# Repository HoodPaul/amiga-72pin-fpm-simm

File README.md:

# Amiga 72-pin FPM SIMM

A common PCB for **4 MB single-sided** and **8 MB double-sided** 5 V FPM SIMMs, developed for Amiga 4000 motherboard memory configurations. Current revision: **A7**.

The project began with a wish to make RAM that visually matches Re-Amiga systems: **black PCB, white silkscreen and gold contacts and exposed pads**. It is a collaboration between **Paul of UK Computing Limited**, **Jon of JMC Electronics** and **AI assistance through Codex**.

**FIRST SUCCESSFUL HARDWARE TEST: 7 November 2026.** Five custom Rev A7 SIMMs installed in an Amiga 4000D were recognised by Kickstart Memory Scan as **18.00 MB total (2.00 MB Chip RAM + 16.00 MB Fast RAM)**. The Chip RAM socket contained one physically **8 MB double-sided** module, recognised as **2 MB Chip RAM**; the four Fast RAM sockets contained four **4 MB front-only** modules. Paul reports the machine alive and working. This establishes initial detection and operation, not a completed extended memory, refresh, retention or graphics/DMA diagnostic. See the [first hardware test report](docs/2026-11-07-FIRST-A4000D-HARDWARE-TEST.md).

**Previous manufacturing milestone, 24 October 2026:** All 15 JLCPCB PCBs were reported manufactured and in transit. Five have since been assembled and demonstrated in the host. Exact receipt date, full shipment count and finished-board measurements have not been recorded. See the [manufacturing record](docs/FABRICATION-OPTIONS.md) and [production-file review](docs/JLCPCB-PRODUCTION-REVIEW.md).

For another engineer or AI picking up the project, start with [AGENTS.md](AGENTS.md), the [current AI handover](docs/AI-HANDOVER.md) and the [documentation index](docs/README.md).

These are unpopulated CAD appearance previews: black solder mask, white silkscreen and gold exposed pads. Actual colours and contact plating are fabrication choices.

## PCB and files

Open [HY8M-SIMM.kicad_pro](HY8M-SIMM.kicad_pro) with **KiCad 10.0 or newer**. Project-local symbols and footprints are included.

| Property | Current design |
|---|---|
| Connector | 72-pin SIMM, 32-bit non-parity |
| Outline | 107.95 × 25.4 mm |
| Finished thickness | 1.2 mm ordered; measure finished boards and verify socket fit |
| Copper layers | **Four** |
| F.Cu | Front signals and pads |
| In1.Cu | GND plane |
| In2.Cu | Signals and +5 V copper fill |
| B.Cu | Rear signals and pads |
| Minimum signal track / nominal clearance | 0.20 / 0.20 mm |
| Through vias | 0.60 mm copper diameter / 0.30 mm drill |

In2.Cu is a mixed signal/supply layer. The design does not have separate GND and power planes on this four-layer PCB.

## 70 ns assembly options

Both builds use **HY5118160JC-70** DRAMs and the same PCB. DNP means do not populate.

| Build | DRAM population | Capacitors fitted | R1/R2 | R3/R4 | PD links fitted |
|---|---|---|---|---|---|
| [4 MB / 70 ns](variants/4MB-70ns/BOM.csv) | U1/U2, front only | C1/C2 | DNP | DNP | PD1, PD2, PD3 |
| [8 MB / 70 ns](variants/8MB-70ns/BOM.csv) | U1–U4, both faces | C1–C4 | 0 Ω each | 10 kΩ each | PD3 |

Capacitors are **220 nF (0.22 µF), 0805, X7R, 16 V or higher**. Use new capacitors. Links and pull-ups use 0603 pads. PD4 remains open in both builds.

Separate [60 ns variants](assembly-options.csv) are retained for the verified **HY5118160BJC-60** part. Use the chosen variant's BOM and DNP-marked schematic. Fitting different PD links cannot make a 70 ns chip operate as a 60 ns part.

A true 4 MB single-sided build omits U3/U4, C3/C4 and R1–R4. Disabling the rear rank of a physically double-sided board does not make it a single-sided module for socket clearance.

## Intended Amiga configurations

| Purpose | Intended population |
|---|---|
| 2 MB Chip RAM | One fully populated 8 MB module; intended to use 2 MB and leave 6 MB unaddressed |
| 16 MB Fast RAM | Two 8 MB modules in Fast slots 1 and 3 |
| 16 MB Fast RAM | Four front-only 4 MB modules in Fast slots 1–4 |

Fast-slot numbering excludes the separate Chip RAM socket. **The 8 MB physical Chip module used as 2 MB Chip RAM and four 4 MB Fast modules have now been recognised together on an A4000D (7 November 2026)**. The alternative two-8 MB Fast RAM configuration remains untested. The Chip RAM socket does not gain 8 MB of addressable Chip RAM. See [hardware test evidence](docs/2026-11-07-FIRST-A4000D-HARDWARE-TEST.md) and [compatibility research](docs/compatibility-research.md).

## Donor chips

The Hyundai HY5118160 devices were chosen for their relatively low SOJ package profile and the availability of suitable donor SIMMs on online marketplaces during project planning. This made them a practical starting point for the matching modules while keeping one chip family across the 4 MB and 8 MB builds.

Obtain readable photographs of **every fitted chip on both faces** before buying a donor. The specified 70 ns device is **HY5118160JC-70**: 5 V, 1M×16, FPM, 42-pin 400 mil SOJ, 1K refresh. The separately verified 60 ns alternative is **HY5118160BJC-60**.

An “8 MB / 2M×32 / 72-pin” listing or bare PCB number does not identify its chips. **HY5118164 is EDO**, and **HY5116160B has a different refresh organisation**; neither is the specified donor. Confirm the complete marking and datasheet rather than relying on similar part numbers.

### Most likely alternative DRAMs (not yet tested)

The **LG/GoldStar GM71C18160CJ-7 (70 ns)**, **GM71C18160CJ-6 (60 ns)**, **Samsung KM416C1200AJ-7 (70 ns)** and **KM416C1200AJ-6 (60 ns)** are promising **5 V, 1M × 16, FPM, 1K-refresh, 42-pin SOJ** candidates. **All four remain untested on Rev A7**, with no proven donor-board or Amiga hardware result. Confirm the exact part's pinout, package, refresh and timing before using it. See the [LG/Samsung alternative comparison and source links](docs/compatibility-research.md#high-confidence-lggoldstar-and-samsung-alternatives-untested-9-november-2026).

Test the intact donor before desoldering and record orientation/pin 1. One healthy four-chip donor can supply one 8 MB board or two 4 MB boards, assuming all devices survive removal. This project does not certify donor authenticity, seller stock or recovered-chip health.

## Prototype fabrication and remaining checks

- **Current order:** four layers, 1.2 mm nominal, 1 oz copper on all layers, black mask, white silkscreen, **ENIG 2 microinch**, ink-plugged vias, **no bevel**, deburring, no edge plating and no manufacturer mark. See the [ordering settings and screenshots](docs/FABRICATION-OPTIONS.md).
- **Contacts:** the native pad setback is **0.2286 mm**; CAM copper compensation leaves approximately **0.221 mm**. The original 144 findings against the generic 0.50 mm edge rule remain documented. The reviewed CAM preserves all contacts and functional connections; this is specific to this prototype package, not blanket approval for other manufacturers or bevel processes.
- **Finish and fit:** the selected ENIG prototype finish differs from the earlier selective hard-gold proposal. Hard gold offers better wear resistance for repeated insertion. Measure the finished connector thickness and inspect edge quality, SOJ fit and socket/case clearance before use. Substantial hand bevelling could cut into the plated contacts.

The retaining holes are closed circular Edge.Cuts profiles in the source; JLCPCB converted these to **3.18 mm finished non-plated holes** with compensated 3.25 mm tools. Use the [four-layer file map](docs/layer-file-map.txt) and read [fabrication notes](fabrication-review/READ-BEFORE-ORDERING.txt). The common paste layers include all footprints; assembly/stencil use must follow the chosen BOM.

## Checks and limitations

The saved design has **864 track segments, 195 vias and zero unconnected items**. The [exact copper comparison](docs/copper-comparison.txt) confirms unchanged routing, pads, component placements, outline and filled copper between A3–A6, the user-edited PCB and A7. The independent mapping review passes 321 assertions.

**144 contact-edge errors and 46 schematic-parity warnings remain documented.** Existing project settings ignore seven check types; no ERC report is included. Read [validation.txt](docs/validation.txt) and the [native DRC report](docs/drc-routed.json) for the scope and remaining findings. CAD checks do not establish timing, refresh, signal integrity or operation in an Amiga.

Run the portable preservation audit from the repository root:

```sh
python3 source/compare_copper.py
```

The current silkscreen preserves the manually edited layout, with UK Computing artwork on the front left and JMC on the front right. Rear assembly notes and PD tables sit beneath the rear chip bodies. Historical generator scripts can overwrite custom artwork; use the [development workflow](source/WORKFLOW.md).

## Project contents

| Path | Purpose |
|---|---|
| [BOM.csv](BOM.csv), [assembly-options.csv](assembly-options.csv) | Population comparison |
| [variants/](variants/) | Four assembly BOMs and DNP-marked schematics |
| [previews/](previews/) | Native layer plots, schematic and appearance views |
| [fabrication-review/](fabrication-review/) | Draft Gerbers, drills and fabrication notes |
| [docs/](docs/) | Pin map, research and validation reports |
| [source/](source/) | Artwork baseline, reference PCB and development/verification tools |
| [Assembly guide](docs/ASSEMBLY.md) | 70 ns parts, fitting and system quantities |
| [Component ordering](docs/COMPONENT-ORDERING.md) | DigiKey parts and quantities for either ten single-sided or ten double-sided modules, with spares |
| [Fabrication options](docs/FABRICATION-OPTIONS.md) | Current JLCPCB order and historical PCBWay quotation |
| [PCB ordering screenshots](docs/FABRICATION-OPTIONS.md#jlcpcb-ordering-screenshots) | JLCPCB settings, four-layer sequence and earlier PCBWay reminders |
| [JLCPCB production review](docs/JLCPCB-PRODUCTION-REVIEW.md) | Original-to-CAM comparison, compensated drills and confirmation action |
| [Project history](docs/PROJECT-HISTORY.md) | A1–A7 development record |
| [NOTICE.md](NOTICE.md) | Template attribution and supplied artwork |

## Attribution

Project collaboration: **Paul, UK Computing Limited; Jon, JMC Electronics; and AI assistance through Codex**. The collaborators ask that the UK Computing and JMC artwork remains in its existing positions on shared versions and manufactured boards derived from this design, with the project and template credits retained. See [attribution and supplied artwork](NOTICE.md).

The mechanical starting point is [wiretap-retro/72-pin-SIMM-KiCAD-Template](https://github.com/wiretap-retro/72-pin-SIMM-KiCAD-Template). Its original [template README](source/template-README.md) and [PCB template](source/template.kicad_pcb) are retained. Circuit/package facts come from Hyundai documentation; host behaviour and PD codes are sourced in [compatibility research](docs/compatibility-research.md).

This project is not a measured clone of PCB P1004B746400 / B7464 Rev.A.

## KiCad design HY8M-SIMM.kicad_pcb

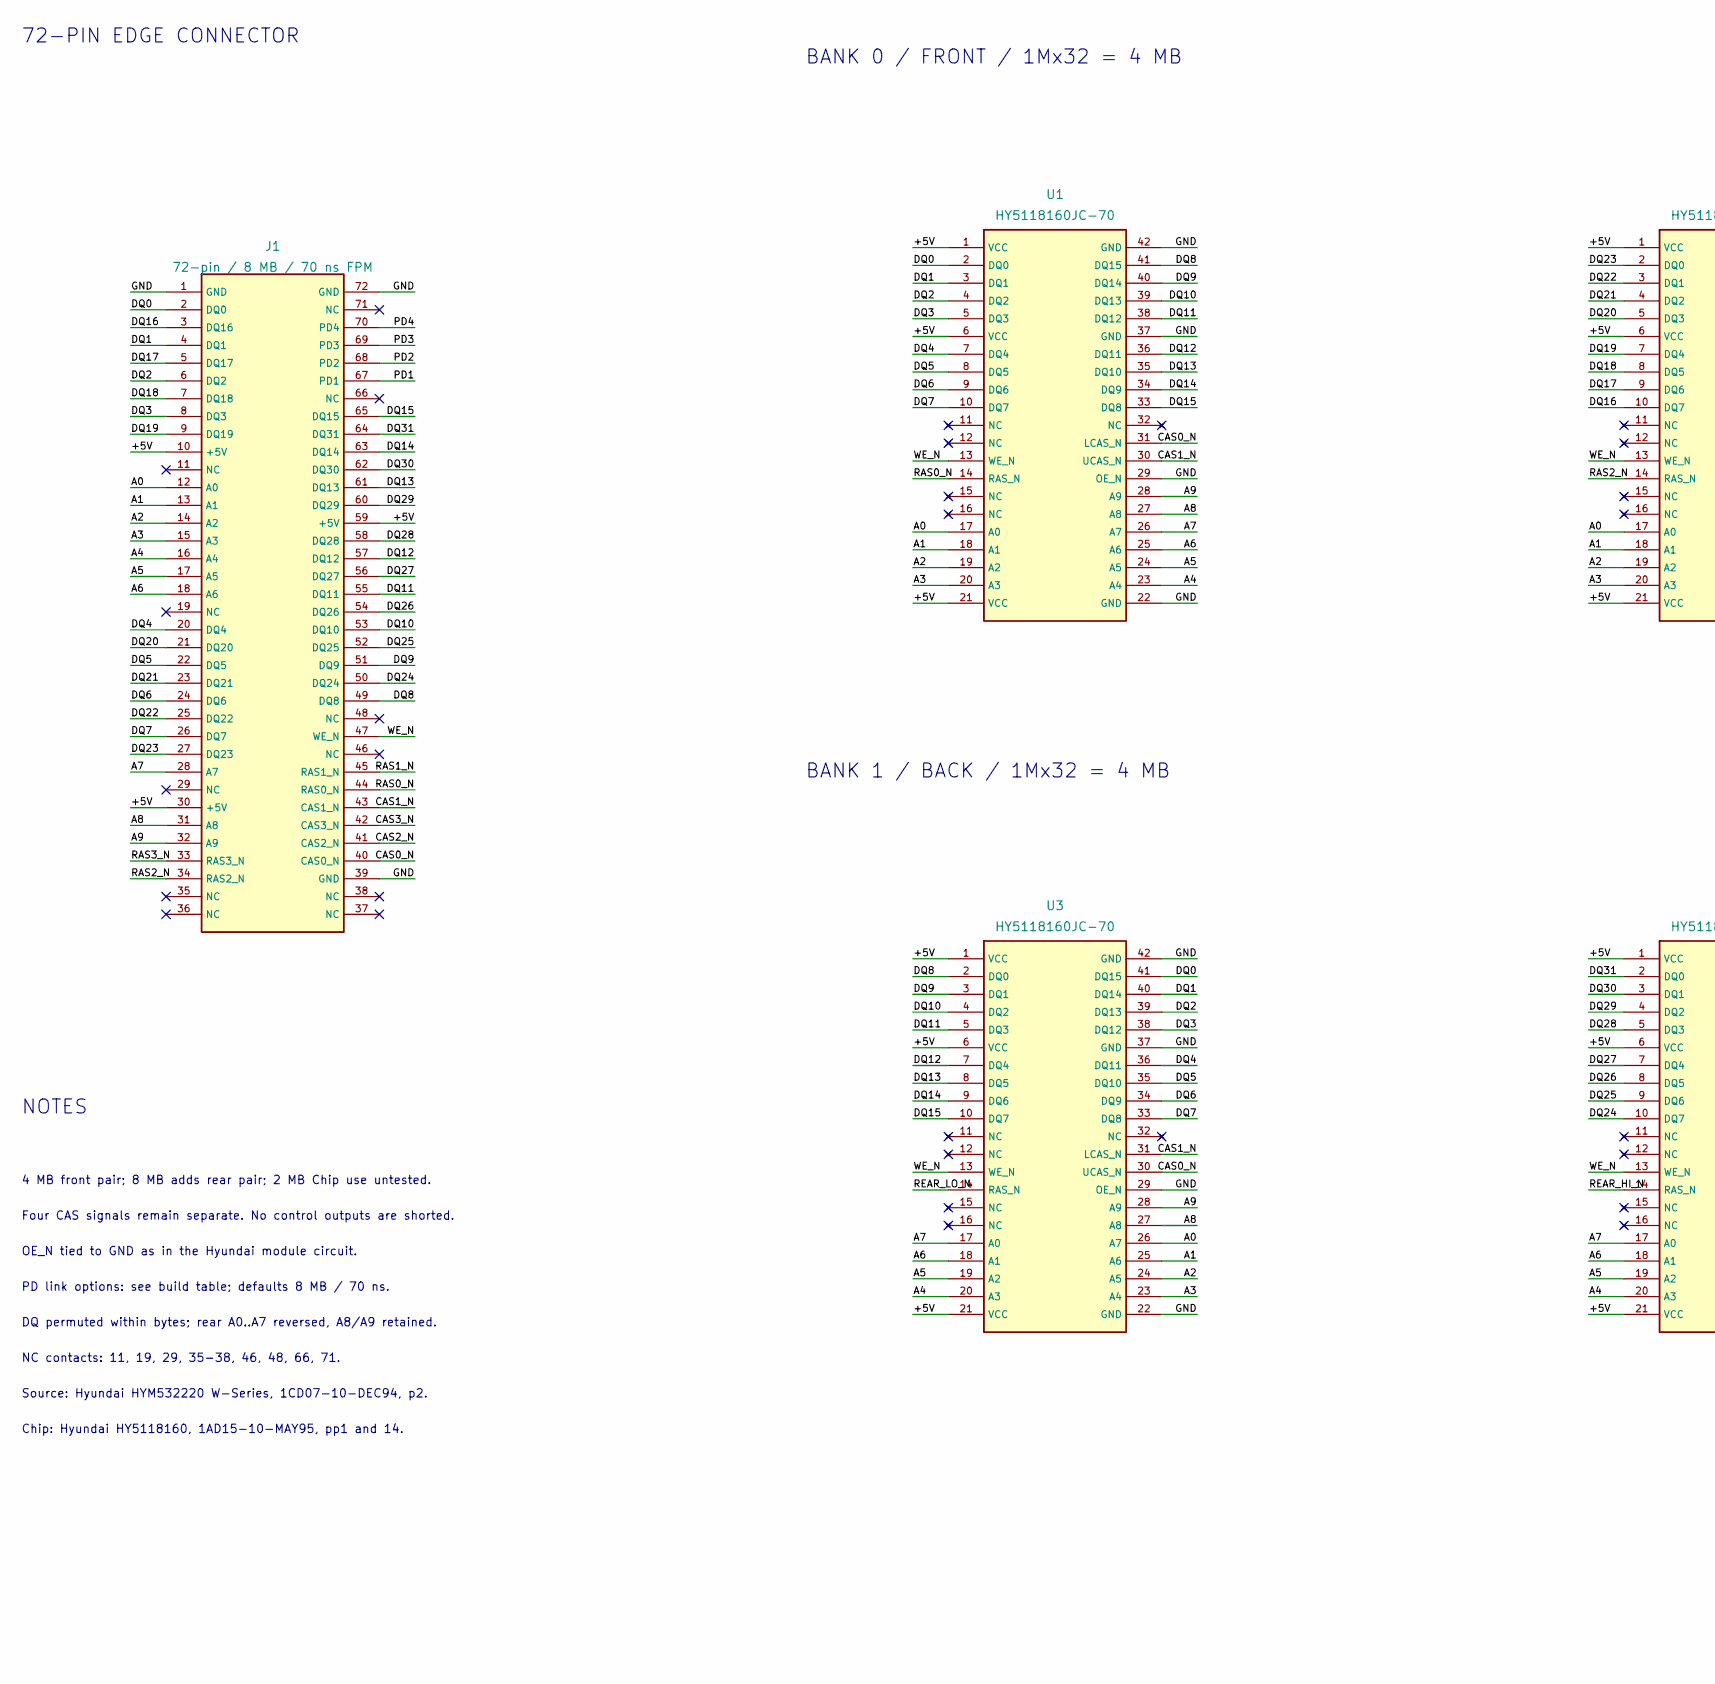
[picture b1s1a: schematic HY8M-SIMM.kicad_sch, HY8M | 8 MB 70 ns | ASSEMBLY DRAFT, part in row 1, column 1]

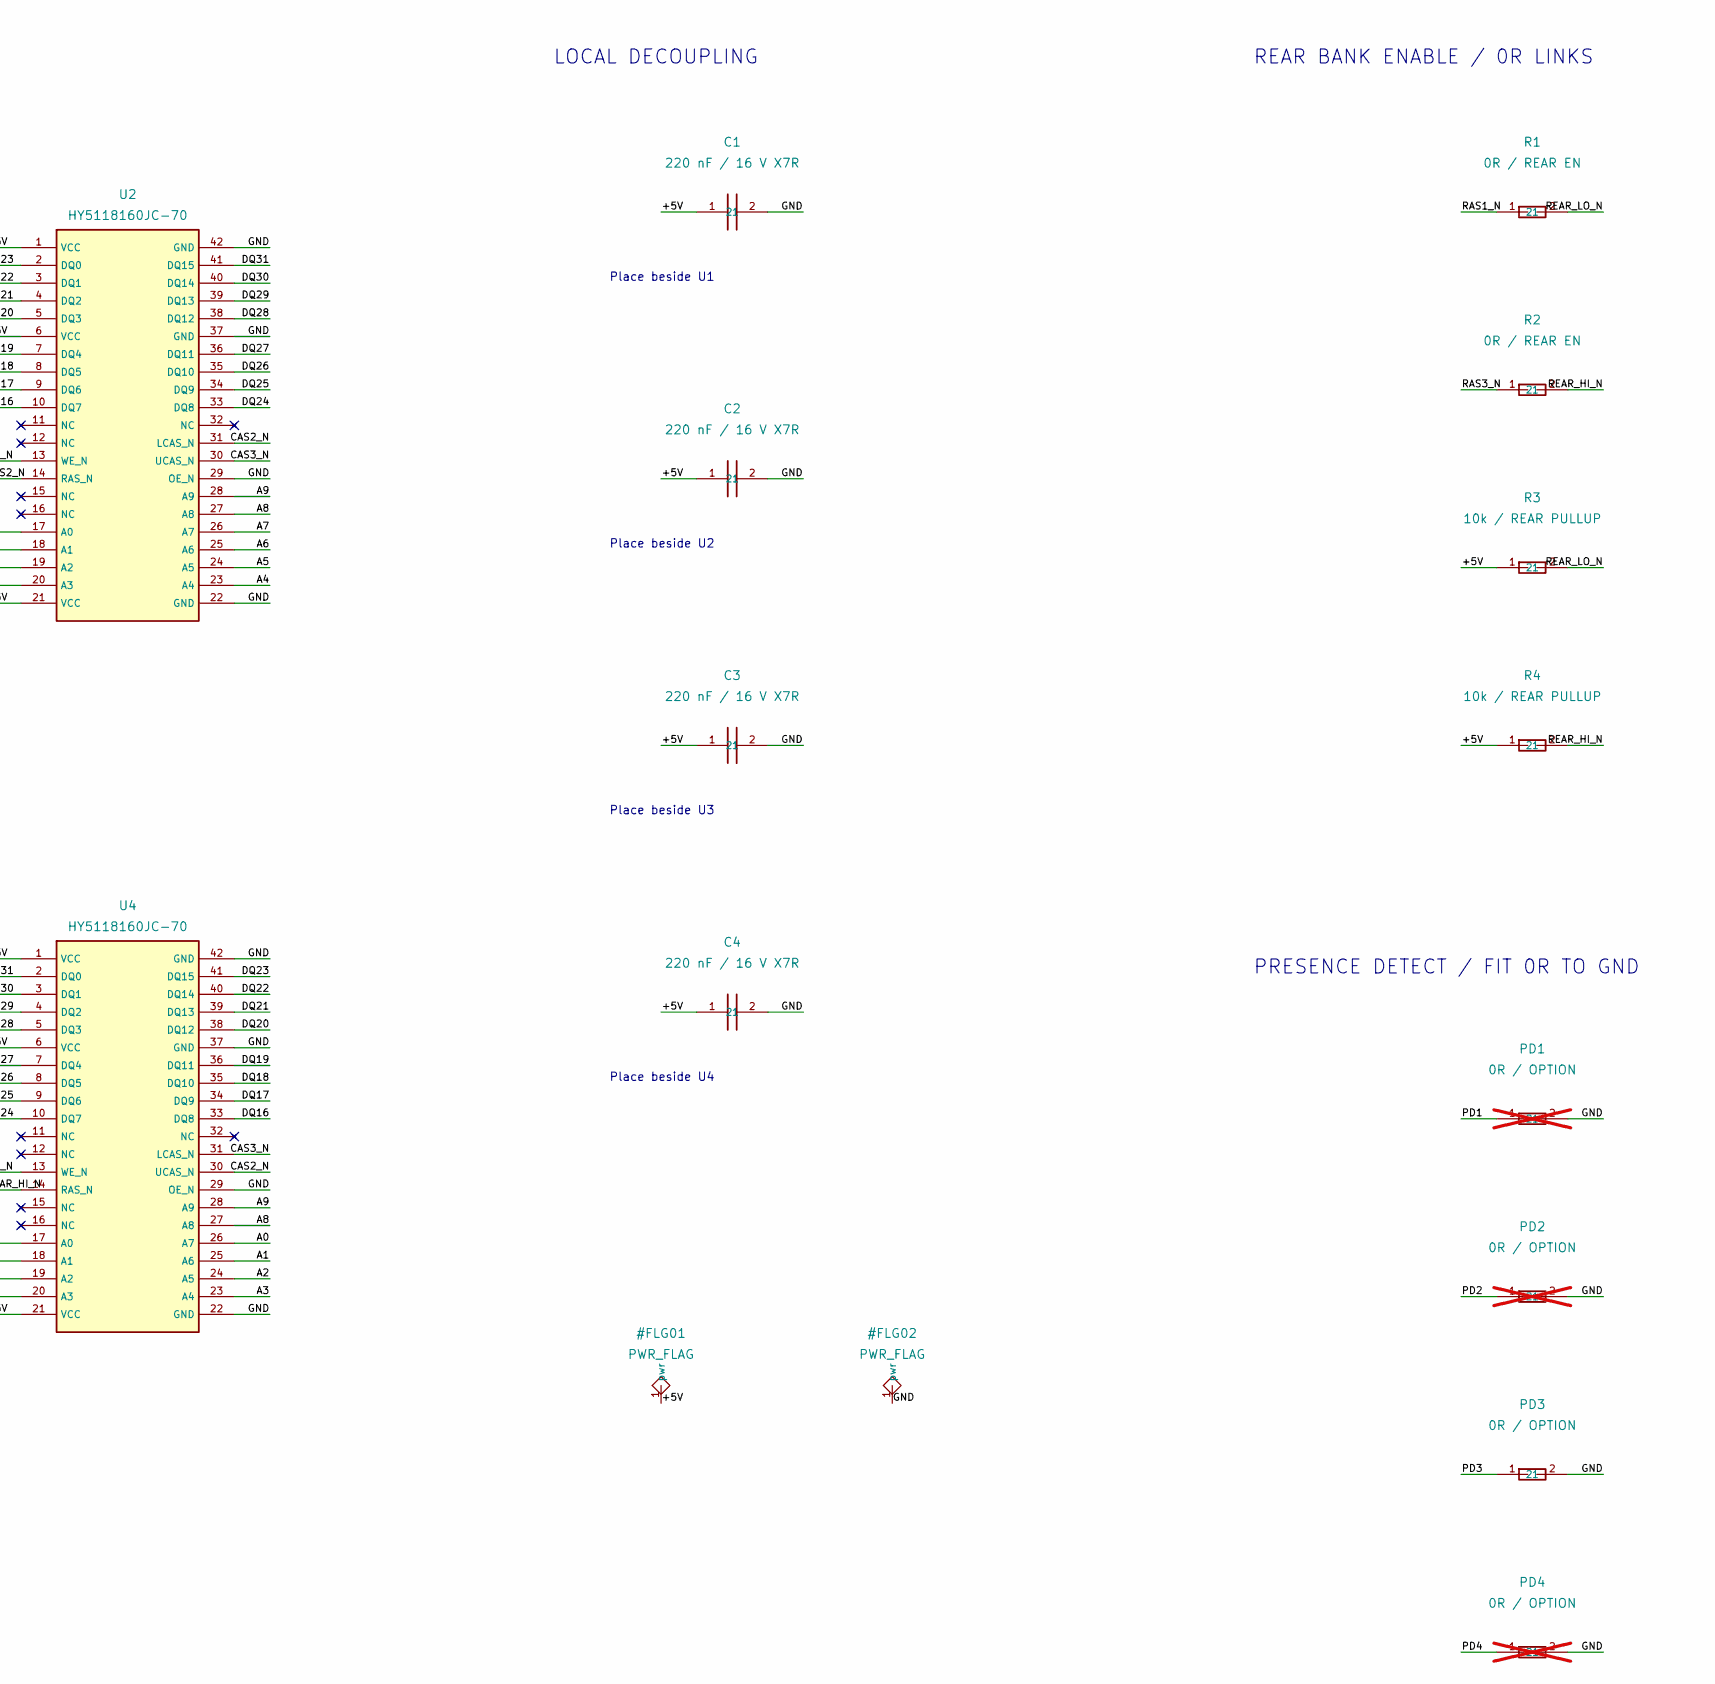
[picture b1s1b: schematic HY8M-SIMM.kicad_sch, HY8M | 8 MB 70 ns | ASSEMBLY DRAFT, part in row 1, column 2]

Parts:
C1, C2, C3, C4: 220 nF / 16 V X7R; C_0805
J1: 72-pin / 8 MB / 70 ns FPM; SIMM72
PD1, PD2, PD4: 0R / OPTION; R_0603; not fitted
PD3: 0R / OPTION; R_0603
R1, R2: 0R / REAR EN; R_0603
R3, R4: 10k / REAR PULLUP; R_0603
U1, U2, U3, U4: HY5118160JC-70; SOJ42_400mil

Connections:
/+5V: C1.1, C2.1, C3.1, C4.1, J1.10 (+5V), J1.30 (+5V), J1.59 (+5V), R3.1, R4.1, U1.1 (VCC), U1.6 (VCC), U1.21 (VCC), U2.1 (VCC), U2.6 (VCC), U2.21 (VCC), U3.1 (VCC), U3.6 (VCC), U3.21 (VCC), U4.1 (VCC), U4.6 (VCC), U4.21 (VCC)
/A0: J1.12 (A0), U1.17 (A0), U2.17 (A0), U3.26 (A7), U4.26 (A7)
/A1: J1.13 (A1), U1.18 (A1), U2.18 (A1), U3.25 (A6), U4.25 (A6)
/A2: J1.14 (A2), U1.19 (A2), U2.19 (A2), U3.24 (A5), U4.24 (A5)
/A3: J1.15 (A3), U1.20 (A3), U2.20 (A3), U3.23 (A4), U4.23 (A4)
/A4: J1.16 (A4), U1.23 (A4), U2.23 (A4), U3.20 (A3), U4.20 (A3)
/A5: J1.17 (A5), U1.24 (A5), U2.24 (A5), U3.19 (A2), U4.19 (A2)
/A6: J1.18 (A6), U1.25 (A6), U2.25 (A6), U3.18 (A1), U4.18 (A1)
/A7: J1.28 (A7), U1.26 (A7), U2.26 (A7), U3.17 (A0), U4.17 (A0)
/A8: J1.31 (A8), U1.27 (A8), U2.27 (A8), U3.27 (A8), U4.27 (A8)
/A9: J1.32 (A9), U1.28 (A9), U2.28 (A9), U3.28 (A9), U4.28 (A9)
/CAS0_N: J1.40 (CAS0_N), U1.31 (LCAS_N), U3.30 (UCAS_N)
/CAS1_N: J1.43 (CAS1_N), U1.30 (UCAS_N), U3.31 (LCAS_N)
/CAS2_N: J1.41 (CAS2_N), U2.31 (LCAS_N), U4.30 (UCAS_N)
/CAS3_N: J1.42 (CAS3_N), U2.30 (UCAS_N), U4.31 (LCAS_N)
/DQ0: J1.2 (DQ0), U1.2 (DQ0), U3.41 (DQ15)
/DQ1: J1.4 (DQ1), U1.3 (DQ1), U3.40 (DQ14)
/DQ2: J1.6 (DQ2), U1.4 (DQ2), U3.39 (DQ13)
/DQ3: J1.8 (DQ3), U1.5 (DQ3), U3.38 (DQ12)
/DQ4: J1.20 (DQ4), U1.7 (DQ4), U3.36 (DQ11)
/DQ5: J1.22 (DQ5), U1.8 (DQ5), U3.35 (DQ10)
/DQ6: J1.24 (DQ6), U1.9 (DQ6), U3.34 (DQ9)
/DQ7: J1.26 (DQ7), U1.10 (DQ7), U3.33 (DQ8)
/DQ8: J1.49 (DQ8), U1.41 (DQ15), U3.2 (DQ0)
/DQ9: J1.51 (DQ9), U1.40 (DQ14), U3.3 (DQ1)
/DQ10: J1.53 (DQ10), U1.39 (DQ13), U3.4 (DQ2)
/DQ11: J1.55 (DQ11), U1.38 (DQ12), U3.5 (DQ3)
/DQ12: J1.57 (DQ12), U1.36 (DQ11), U3.7 (DQ4)
/DQ13: J1.61 (DQ13), U1.35 (DQ10), U3.8 (DQ5)
/DQ14: J1.63 (DQ14), U1.34 (DQ9), U3.9 (DQ6)
/DQ15: J1.65 (DQ15), U1.33 (DQ8), U3.10 (DQ7)
/DQ16: J1.3 (DQ16), U2.10 (DQ7), U4.33 (DQ8)
/DQ17: J1.5 (DQ17), U2.9 (DQ6), U4.34 (DQ9)
/DQ18: J1.7 (DQ18), U2.8 (DQ5), U4.35 (DQ10)
/DQ19: J1.9 (DQ19), U2.7 (DQ4), U4.36 (DQ11)
/DQ20: J1.21 (DQ20), U2.5 (DQ3), U4.38 (DQ12)
/DQ21: J1.23 (DQ21), U2.4 (DQ2), U4.39 (DQ13)
/DQ22: J1.25 (DQ22), U2.3 (DQ1), U4.40 (DQ14)
/DQ23: J1.27 (DQ23), U2.2 (DQ0), U4.41 (DQ15)
/DQ24: J1.50 (DQ24), U2.33 (DQ8), U4.10 (DQ7)
/DQ25: J1.52 (DQ25), U2.34 (DQ9), U4.9 (DQ6)
/DQ26: J1.54 (DQ26), U2.35 (DQ10), U4.8 (DQ5)
/DQ27: J1.56 (DQ27), U2.36 (DQ11), U4.7 (DQ4)
/DQ28: J1.58 (DQ28), U2.38 (DQ12), U4.5 (DQ3)
/DQ29: J1.60 (DQ29), U2.39 (DQ13), U4.4 (DQ2)
/DQ30: J1.62 (DQ30), U2.40 (DQ14), U4.3 (DQ1)
/DQ31: J1.64 (DQ31), U2.41 (DQ15), U4.2 (DQ0)
/GND: C1.2, C2.2, C3.2, C4.2, J1.1 (GND), J1.39 (GND), J1.72 (GND), PD1.2, PD2.2, PD3.2, PD4.2, U1.22 (GND), U1.29 (OE_N), U1.37 (GND), U1.42 (GND), U2.22 (GND), U2.29 (OE_N), U2.37 (GND), U2.42 (GND), U3.22 (GND), U3.29 (OE_N), U3.37 (GND), U3.42 (GND), U4.22 (GND), U4.29 (OE_N), U4.37 (GND), U4.42 (GND)
/PD1: J1.67 (PD1), PD1.1
/PD2: J1.68 (PD2), PD2.1
/PD3: J1.69 (PD3), PD3.1
/PD4: J1.70 (PD4), PD4.1
/RAS0_N: J1.44 (RAS0_N), U1.14 (RAS_N)
/RAS1_N: J1.45 (RAS1_N), R1.1
/RAS2_N: J1.34 (RAS2_N), U2.14 (RAS_N)
/RAS3_N: J1.33 (RAS3_N), R2.1
/REAR_HI_N: R2.2, R4.2, U4.14 (RAS_N)
/REAR_LO_N: R1.2, R3.2, U3.14 (RAS_N)
/WE_N: J1.47 (WE_N), U1.13 (WE_N), U2.13 (WE_N), U3.13 (WE_N), U4.13 (WE_N)

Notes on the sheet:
72-PIN EDGE CONNECTOR
BANK 0 / FRONT / 1Mx32 = 4 MB
BANK 1 / BACK / 1Mx32 = 4 MB
LOCAL DECOUPLING
Place beside U1
Place beside U2
Place beside U3
Place beside U4
REAR BANK ENABLE / 0R LINKS
PRESENCE DETECT / FIT 0R TO GND
NOTES
4 MB front pair; 8 MB adds rear pair; 2 MB Chip use untested.
Four CAS signals remain separate. No control outputs are shorted.
OE_N tied to GND as in the Hyundai module circuit.
PD link options: see build table; defaults 8 MB / 70 ns.
DQ permuted within bytes; rear A0..A7 reversed, A8/A9 retained.
NC contacts: 11, 19, 29, 35-38, 46, 48, 66, 71.
Source: Hyundai HYM532220 W-Series, 1CD07-10-DEC94, p2.
Chip: Hyundai HY5118160, 1AD15-10-MAY95, pp1 and 14.

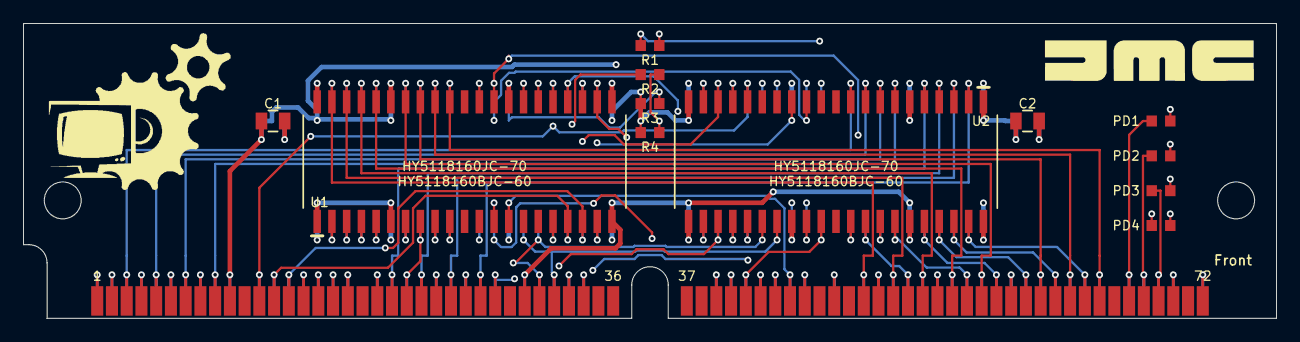
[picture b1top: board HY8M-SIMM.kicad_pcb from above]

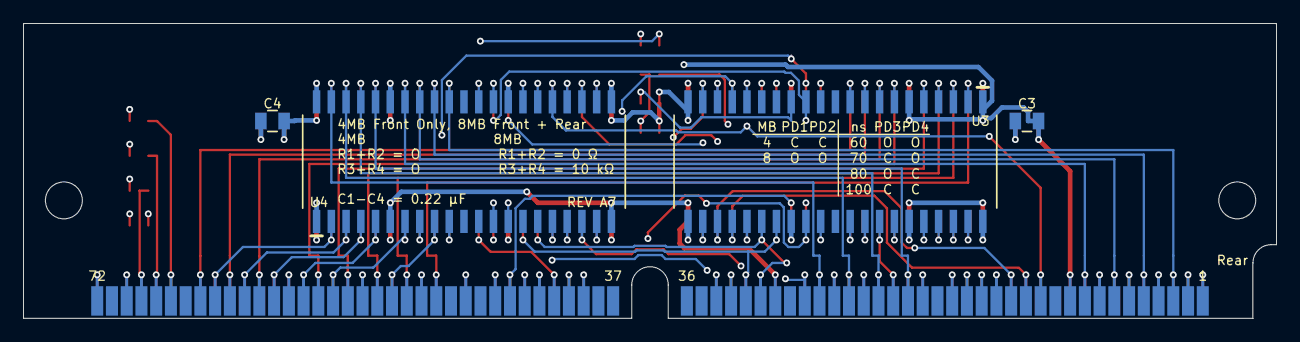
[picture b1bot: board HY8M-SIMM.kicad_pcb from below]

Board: 4 copper layers, 107.9 x 25.4 mm, 17 parts (4 on the bottom side), 59 nets.

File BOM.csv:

Reference,70ns_value,60ns_value,Package,4MB-60ns,4MB-70ns,8MB-60ns,8MB-70ns,Notes
PCB,HY8M A7,HY8M A7,72-pin SIMM,1,1,1,1,Common four-layer 107.95 x 25.4 mm board; proposed 1.2 mm thickness
C1,220 nF,220 nF,0805,1,1,1,1,220 nF; 0805; 16 V or higher; X7R; +/-10%; fit new capacitors.
C2,220 nF,220 nF,0805,1,1,1,1,220 nF; 0805; 16 V or higher; X7R; +/-10%; fit new capacitors.
C3,220 nF,220 nF,0805,0,0,1,1,220 nF; 0805; 16 V or higher; X7R; +/-10%; fit new capacitors.
C4,220 nF,220 nF,0805,0,0,1,1,220 nF; 0805; 16 V or higher; X7R; +/-10%; fit new capacitors.
PD1,0 ohm,0 ohm,0603,1,1,0,0,0 ohm link from PD pin to GND. Unfitted means electrically open.
PD2,0 ohm,0 ohm,0603,1,1,0,0,0 ohm link from PD pin to GND. Unfitted means electrically open.
PD3,0 ohm,0 ohm,0603,0,1,0,1,0 ohm link from PD pin to GND. Unfitted means electrically open.
PD4,0 ohm,0 ohm,0603,0,0,0,0,0 ohm link from PD pin to GND. Unfitted means electrically open.
R1,0 ohm,0 ohm,0603,0,0,1,1,0 ohm rear low-halfword RAS enable. Fit with R2 for 8 MB.
R2,0 ohm,0 ohm,0603,0,0,1,1,0 ohm rear high-halfword RAS enable. Fit with R1 for 8 MB.
R3,10 kohm,10 kohm,0603,0,0,1,1,10 kohm rear low-halfword RAS pull-up to +5 V.
R4,10 kohm,10 kohm,0603,0,0,1,1,10 kohm rear high-halfword RAS pull-up to +5 V.
U1,HY5118160JC-70,HY5118160BJC-60,SOJ42 400 mil,1,1,1,1,42-pin 400 mil SOJ; 5 V; 1Mx16; FPM; 1K refresh. Readable exact donor marking required.
U2,HY5118160JC-70,HY5118160BJC-60,SOJ42 400 mil,1,1,1,1,42-pin 400 mil SOJ; 5 V; 1Mx16; FPM; 1K refresh. Readable exact donor marking required.
U3,HY5118160JC-70,HY5118160BJC-60,SOJ42 400 mil,0,0,1,1,42-pin 400 mil SOJ; 5 V; 1Mx16; FPM; 1K refresh. Readable exact donor marking required.
U4,HY5118160JC-70,HY5118160BJC-60,SOJ42 400 mil,0,0,1,1,42-pin 400 mil SOJ; 5 V; 1Mx16; FPM; 1K refresh. Readable exact donor marking required.

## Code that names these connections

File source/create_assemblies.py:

#!/usr/bin/env python3
"""Create population BOMs and DNP-marked schematics for the common A7 PCB."""
from pathlib import Path
import json,re,csv,shutil
r=Path(__file__).resolve().parent.parent
base=(r/'HY8M-SIMM.kicad_sch').read_text()
all_refs={f'U{i}' for i in range(1,5)}|{f'C{i}' for i in range(1,5)}|{f'R{i}' for i in range(1,5)}|{f'PD{i}' for i in range(1,5)}
variants={}
for size in [4,8]:
 for speed in [60,70]:
  tag=f'{size}MB-{speed}ns';fitted={'U1','U2','C1','C2'}
  if size==8:fitted|={'U3','U4','C3','C4','R1','R2','R3','R4'}
  pd=[size==4,size==4,speed==70,False]
  fitted|={f'PD{i+1}' for i,on in enumerate(pd) if on}
  variants[tag]={'capacity_mib':size,'speed_ns':speed,'dram_mpn':'HY5118160BJC-60' if speed==60 else 'HY5118160JC-70','fitted':sorted(fitted),'dnp':sorted(all_refs-fitted),'pd_grounded':pd,'rear_enabled':size==8}
def blocks(s):
 for m in re.finditer(r'^\(symbol \(lib_id ',s,re.M):
  i=m.start();depth=0;quoted=False;escape=False
  for j in range(i,len(s)):
   c=s[j]
   if quoted:
    if escape:escape=False
    elif c=='\\':escape=True
    elif c=='"':quoted=False
   elif c=='"':quoted=True
   elif c=='(':depth+=1
   elif c==')':
    depth-=1
    if depth==0:yield i,j+1,s[i:j+1];break
def make_schematic(v):
 s=base
 for a,z,b in reversed(list(blocks(base))):
  ref=re.search(r'\(property "Reference" "([^"]+)"',b)[1]
  dnp=ref in v['dnp'];b=re.sub(r'\(dnp (?:yes|no)\)',f'(dnp {"yes" if dnp else "no"})',b,count=1)
  if ref.startswith('U'):
   b=re.sub(r'(\(property "Value" )"[^"]+"',lambda m:m[1]+json.dumps(v['dram_mpn']),b,count=1)
  elif ref=='J1':
   value=f'72-pin / {v["capacity_mib"]} MB / {v["speed_ns"]} ns FPM'
   b=re.sub(r'(\(property "Value" )"[^"]+"',lambda m:m[1]+json.dumps(value),b,count=1)
  s=s[:a]+b+s[z:]
 s=re.sub(r'(\(title )"[^"]+"',lambda m:m[1]+json.dumps(f'HY8M | {v["capacity_mib"]} MB {v["speed_ns"]} ns | ASSEMBLY DRAFT'),s,count=1)
 s=re.sub(r'(\(comment 1 )"[^"]+"',lambda m:m[1]+json.dumps(f'{v["dram_mpn"]} x{2 if v["capacity_mib"]==4 else 4} / 5 V / {v["capacity_mib"]} MB populated'),s,count=1)
 return s
(r/'docs/assembly-variants.json').write_text(json.dumps(variants,indent=2)+'\n')
notes={
 'U':'42-pin 400 mil SOJ; 5 V; 1Mx16; FPM; 1K refresh. Readable exact donor marking required.',
 'C':'220 nF; 0805; 16 V or higher; X7R; +/-10%; fit new capacitors.',
 'R1':'0 ohm rear low-halfword RAS enable. Fit with R2 for 8 MB.',
 'R2':'0 ohm rear high-halfword RAS enable. Fit with R1 for 8 MB.',
 'R3':'10 kohm rear low-halfword RAS pull-up to +5 V.',
 'R4':'10 kohm rear high-halfword RAS pull-up to +5 V.',
 'PD':'0 ohm link from PD pin to GND. Unfitted means electrically open.'}
def part(ref,v):
 if ref[0]=='U':return v['dram_mpn'],'SOJ42 400 mil',notes['U']
 if ref[0]=='C':return '220 nF','0805',notes['C']
 if ref.startswith('PD'):return '0 ohm','0603',notes['PD']
 return ('0 ohm' if ref in ['R1','R2'] else '10 kohm'),'0603',notes[ref]
for tag,v in variants.items():
 d=r/'variants'/tag;d.mkdir(parents=True,exist_ok=True)
 sch=make_schematic(v);(d/'HY8M-SIMM.kicad_sch').write_text(sch)
 (d/'sym-lib-table').write_text('(sym_lib_table (lib (name "HY8M")(type "KiCad")(uri "${KIPRJMOD}/../../HY8M.kicad_sym")(options "")(descr "Shared project symbols")))\n')
 (d/'fp-lib-table').write_text('(fp_lib_table (lib (name "HY8M")(type "KiCad")(uri "${KIPRJMOD}/../../HY8M.pretty")(options "")(descr "Shared project footprints")))\n')
 with (d/'BOM.csv').open('w',newline='') as f:
  w=csv.writer(f);w.writerow(['Reference','Quantity','Value_or_MPN','Package','Notes'])
  w.writerow(['PCB',1,'HY8M A7 common PCB','72-pin SIMM','107.95 x 25.4 mm; four layers; 1.2 mm proposed; fabrication review pending'])
  for ref in v['fitted']:w.writerow([ref,1,*part(ref,v)])
 (d/'README.md').write_text(f'''# {tag} assembly

Use the common routed PCB at `../../HY8M-SIMM.kicad_pcb`.
This schematic marks the unfitted components with KiCad DNP flags.
Use this folder's BOM. There is no separate PCB geometry for this assembly.

Fit: {', '.join(v['fitted'])}.

Leave unfitted: {', '.join(v['dnp'])}.

The {v['capacity_mib']} MB build uses {len([x for x in v['fitted'] if x.startswith('U')])} {v['dram_mpn']} devices.
Physical fit, donor health, timing and A4000 operation remain untested.
''')
# Main project is the 8MB/70ns assembly; all four configurations share its copper.
(r/'HY8M-SIMM.kicad_sch').write_text(make_schematic(variants['8MB-70ns']))
with (r/'BOM.csv').open('w',newline='') as f:
 w=csv.writer(f);tags=list(variants);w.writerow(['Reference','70ns_value','60ns_value','Package',*tags,'Notes'])
 w.writerow(['PCB','HY8M A7','HY8M A7','72-pin SIMM',*[1]*4,'Common four-layer 107.95 x 25.4 mm board; proposed 1.2 mm thickness'])
 for ref in sorted(all_refs):
  a,p,n=part(ref,variants['8MB-70ns']);b,_,_=part(ref,variants['8MB-60ns'])
  w.writerow([ref,a,b,p,*[int(ref in variants[tag]['fitted']) for tag in tags],n])
with (r/'assembly-options.csv').open('w',newline='') as f:
 w=csv.writer(f);w.writerow(['Build','DRAM_MPN','Front_chips','Rear_chips','R1_R2','R3_R4','PD1','PD2','PD3','PD4','Intended_use'])
 for tag,v in variants.items():w.writerow([tag,v['dram_mpn'],'U1 U2','U3 U4' if v['rear_enabled'] else 'DNP','0 ohm' if v['rear_enabled'] else 'DNP','10 kohm' if v['rear_enabled'] else 'DNP',*['0 ohm' if on else 'DNP' for on in v['pd_grounded']], 'Fast RAM one rank' if v['capacity_mib']==4 else 'Fast RAM two ranks; intended 2 MB Chip RAM experiment'])
print('Created four assembly options, individual BOMs and DNP schematics')
